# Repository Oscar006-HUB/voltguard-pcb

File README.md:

# VoltGuard PCB

KiCad hardware design for **VoltGuard**, a board built around the ESP32-C3 SuperMini module.

## Contents

| Path | Description |
|------|-------------|
| `voltguard/` | KiCad project: schematic (`.kicad_sch`), PCB layout (`.kicad_pcb`), project files |
| `ESP32-C3_SUPERMINI_TH/` | ESP32-C3 SuperMini symbol, footprint and 3D model (`.step`) |
| `NewSymbols.kicad_sym` | Custom symbol library |
| `NewFootprint.pretty/` | Custom footprint library |

## Opening the project

1. Install [KiCad](https://www.kicad.org/) 8 or later.
2. Open `voltguard/voltguard.kicad_pro`.
3. If symbols or footprints show as missing, add `NewSymbols.kicad_sym` and `NewFootprint.pretty` to the project's symbol and footprint library tables (see `ESP32-C3_SUPERMINI_TH/how-to-import.htm`).

---

Author: **Prince Oscar Mwinnuo** ([@Oscar006-HUB](https://github.com/Oscar006-HUB))

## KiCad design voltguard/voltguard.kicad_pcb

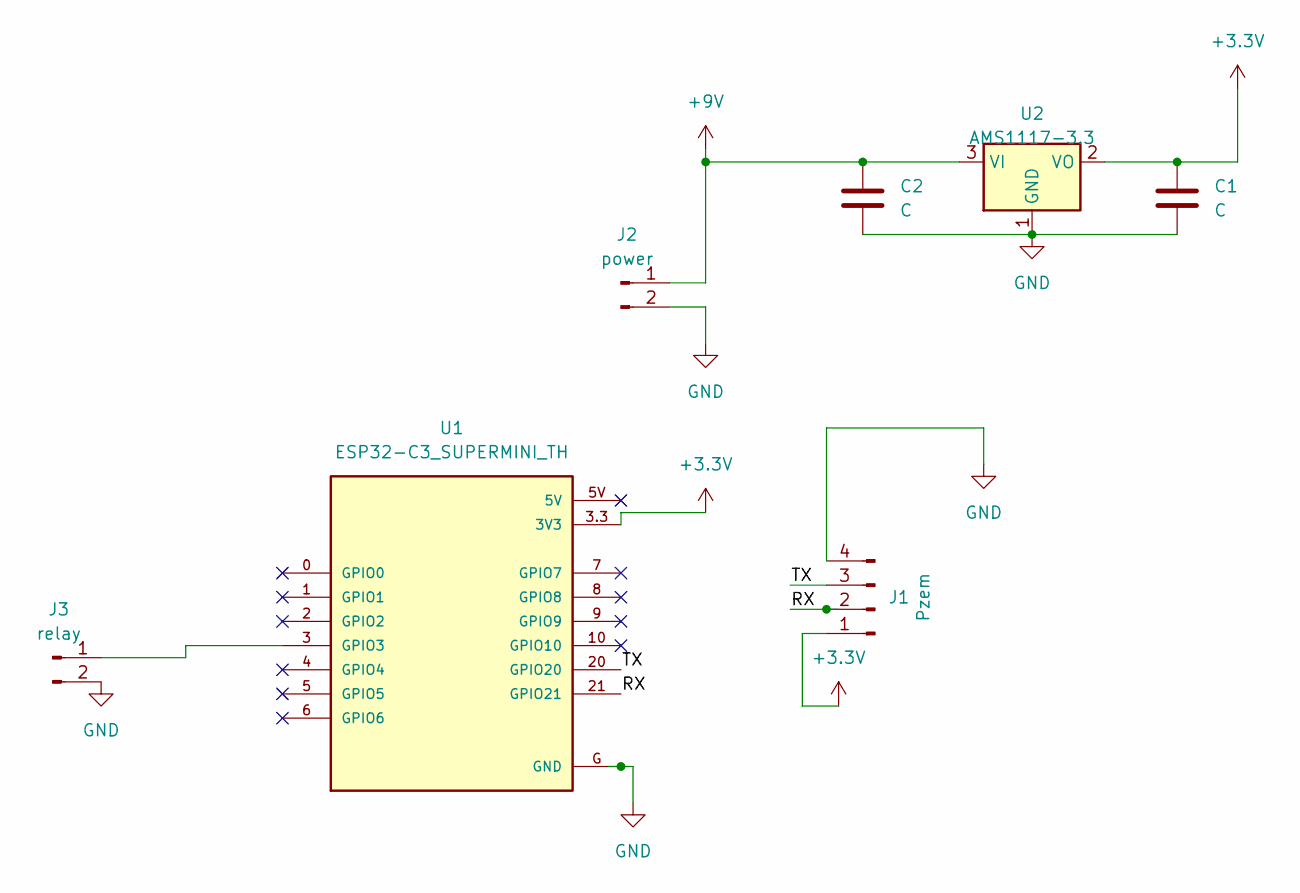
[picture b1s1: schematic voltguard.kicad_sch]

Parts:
C1, C2: C; C_1206_3216Metric
J1: Pzem; PinHeader_1x04_P2.54mm_Horizontal
J2: power; PinHeader_1x02_P2.54mm_Vertical
J3: relay; PinHeader_1x02_P2.54mm_Vertical
U1: ESP32-C3_SUPERMINI_TH; MODULE_ESP32-C3_SUPERMINI_TH
U2: AMS1117-3.3; SOT-223-3_TabPin2

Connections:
+3.3V: C1.1, J1.1, U1.3.3 (3V3), U2.2 (VO)
+9V: C2.1, J2.1, U2.3 (VI)
/RX: J1.2, U1.21 (GPIO21)
/TX: J1.3, U1.20 (GPIO20)
GND: C1.2, C2.2, J1.4, J2.2, J3.2, U1.G (GND), U2.1 (GND)
unnamed: J3.1, U1.3 (GPIO3)

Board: 2 copper layers, 7 parts (0 on the bottom side), 6 nets, no tracks yet.
